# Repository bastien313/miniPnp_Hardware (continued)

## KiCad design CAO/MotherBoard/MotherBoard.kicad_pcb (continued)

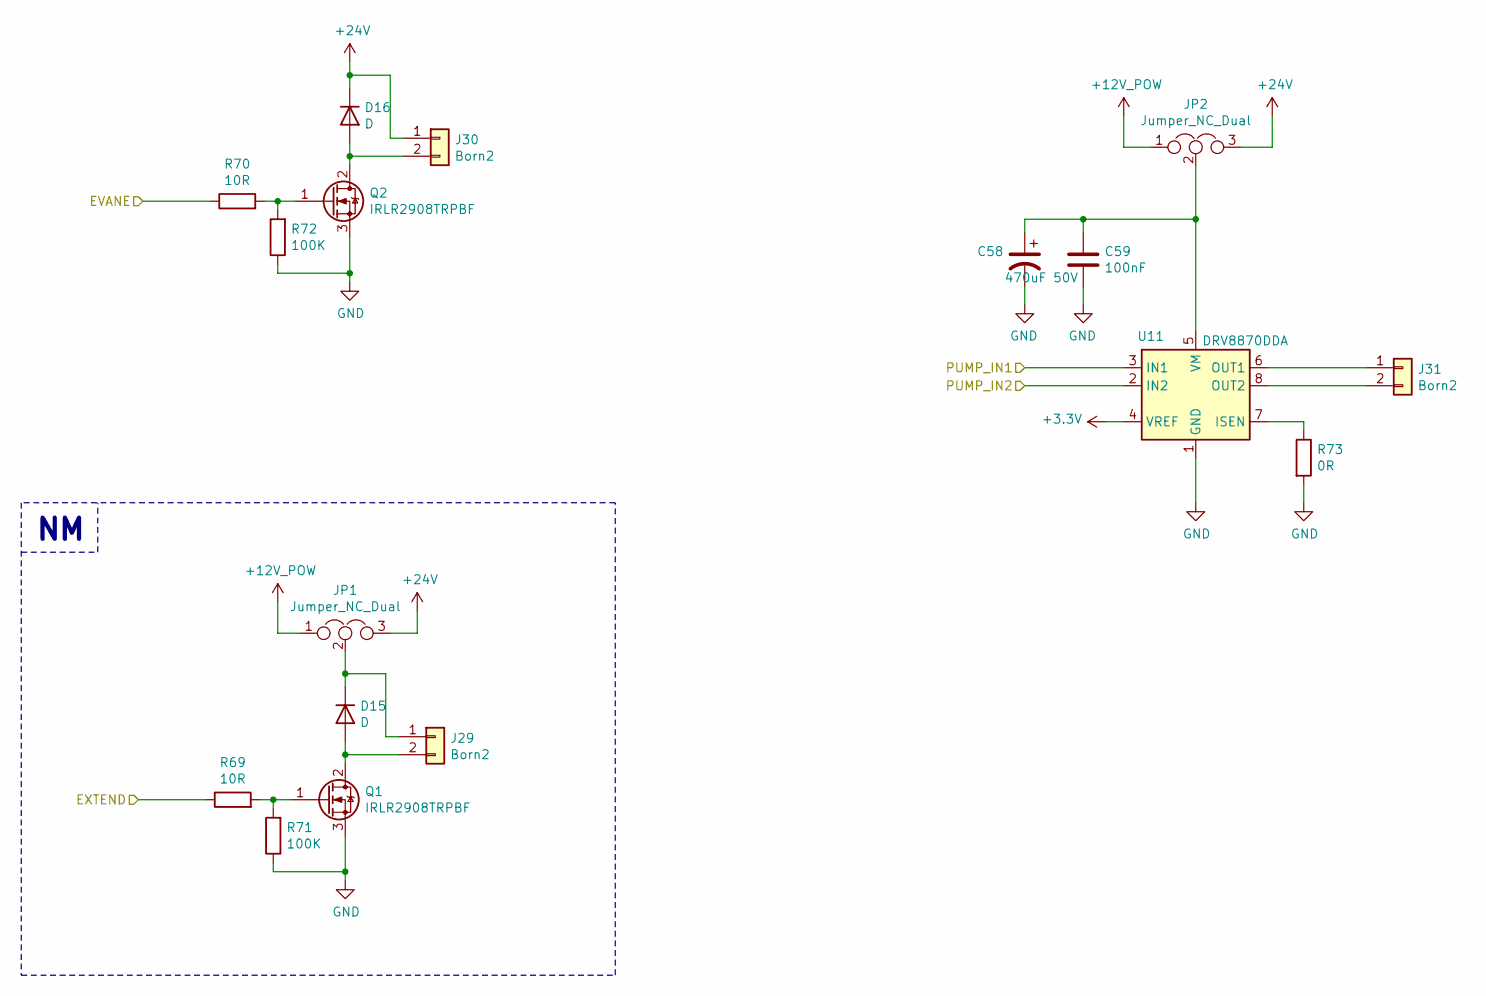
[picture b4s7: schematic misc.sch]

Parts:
C58: 470uF 50V; CP_Radial_D13.0mm_P5.00mm
C59: 100nF; C_0805_2012Metric
D15, D16: D; D_SMB
J29, J30, J31: Born2; TerminalBlock_Phoenix_MKDS-1,5-2-5.08_1x02_P5.08mm_Horizont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
JP1, JP2: Jumper_NC_Dual; PinHeader_1x03_P2.54mm_Vertical
Q1, Q2: IRLR2908TRPBF; TO-252-2
R69, R70: 10R; R_0805_2012Metric_Pad1.15x1.40mm_HandSolder
R71, R72: 100K; R_0805_2012Metric_Pad1.15x1.40mm_HandSolder
R73: 0R; R_2512_6332Metric_Pad1.52x3.35mm_HandSolder
U11: DRV8870DDA; Texas_HTSOP-8-1EP_3.9x4.9mm_P1.27mm_EP2.95x4.9mm_Mask2.4x3.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

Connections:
+12V_POW: JP1.1, JP2.1; also elsewhere on the board
+24V: D16.1 (K), J30.1, JP1.3, JP2.3; also elsewhere on the board
/IO/D20: R70.1; also elsewhere on the board
/IO/D21: R69.1; also elsewhere on the board
/misc/PUMP_IN1: U11.3 (IN1); also elsewhere on the board
/misc/PUMP_IN2: U11.2 (IN2); also elsewhere on the board
unnamed: C58.1, C59.1, JP2.2, U11.5 (VM)
unnamed: D15.1 (K), J29.1, JP1.2
unnamed: D15.2 (A), J29.2, Q1.2 (D)
unnamed: D16.2 (A), J30.2, Q2.2 (D)
unnamed: J31.1, U11.6 (OUT1)
unnamed: J31.2, U11.8 (OUT2)
unnamed: Q1.1 (G), R69.2, R71.2
unnamed: Q2.1 (G), R70.2, R72.2
unnamed: R73.1, U11.7 (ISEN)

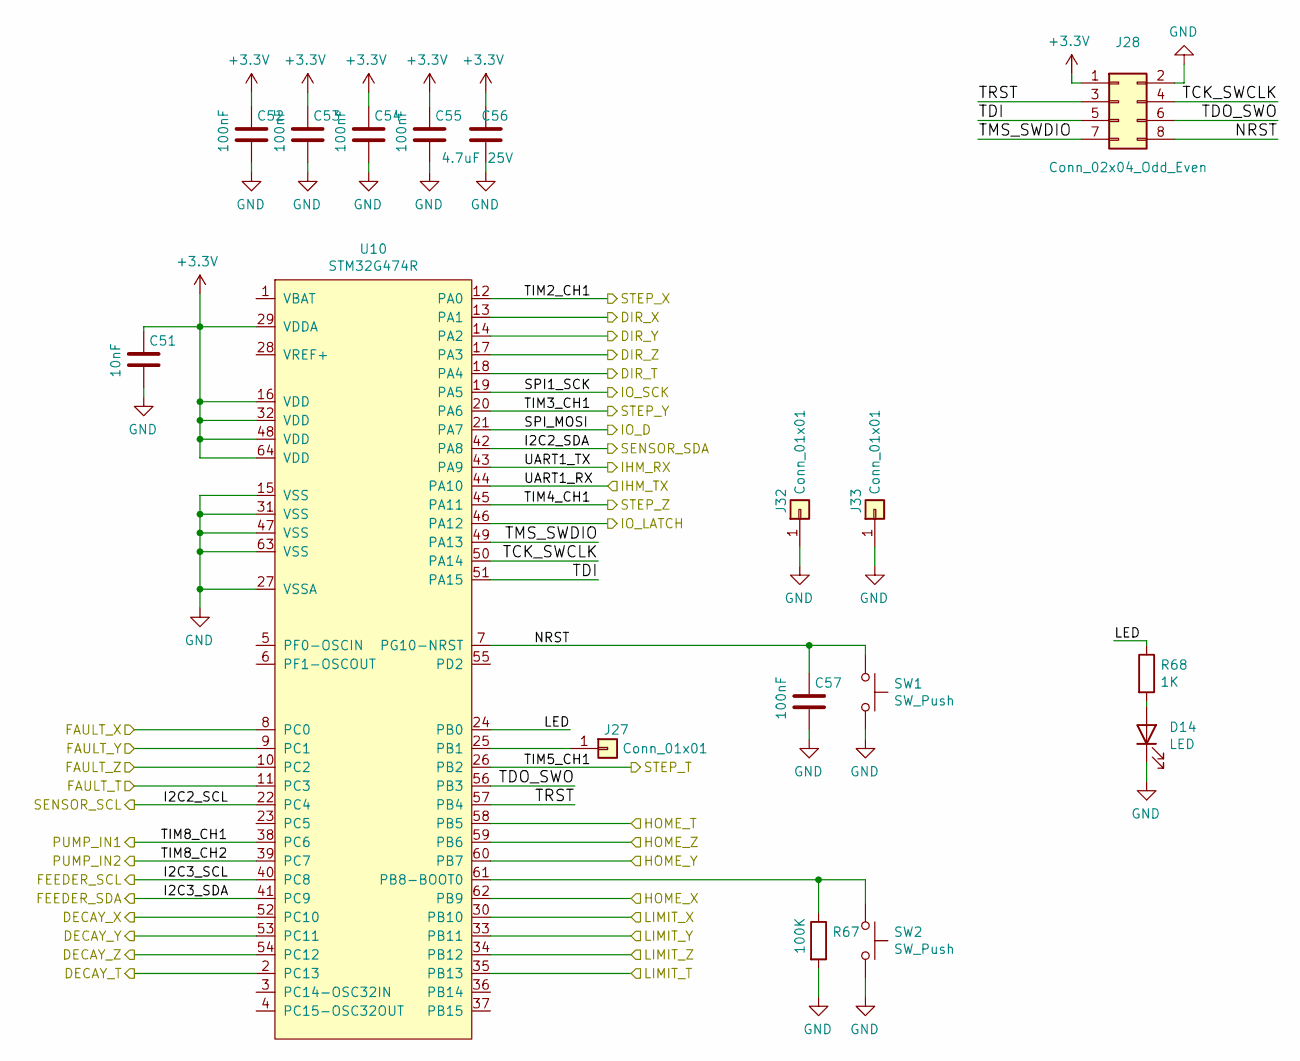
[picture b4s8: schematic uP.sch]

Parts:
C51: 10nF; C_0805_2012Metric
C52, C53, C54, C55, C57: 100nF; C_0805_2012Metric
C56: 4.7uF 25V; C_0805_2012Metric
D14: LED; LED_1206_3216Metric_Castellated
J27, J32, J33: Conn_01x01; Pin_D1.1mm_L8.5mm_W2.5mm_FlatFork
J28: Conn_02x04_Odd_Even; 8Micro-MaTch
R67: 100K; R_0805_2012Metric_Pad1.15x1.40mm_HandSolder
R68: 1K; R_0805_2012Metric_Pad1.15x1.40mm_HandSolder
SW1, SW2: SW_Push; FSM2JSMA
U10: STM32G474R; LQFP-64_10x10mm_P0.5mm

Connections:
/I2C_SENSOR/SCL: U10.22 (PC4); also elsewhere on the board
/I2C_SENSOR/SDA: U10.42 (PA8); also elsewhere on the board
/INPUT/HOME_T: U10.58 (PB5); also elsewhere on the board
/INPUT/HOME_X: U10.62 (PB9); also elsewhere on the board
/IO/CLK: U10.19 (PA5); also elsewhere on the board
/IO/DATA_IN: U10.21 (PA7); also elsewhere on the board
/T/DECAY: U10.2 (PC13); also elsewhere on the board
/T/DIR: U10.18 (PA4); also elsewhere on the board
/T/STEP: U10.26 (PB2); also elsewhere on the board
/X/DECAY: U10.52 (PC10); also elsewhere on the board
/X/DIR: U10.13 (PA1); also elsewhere on the board
/X/STEP: U10.12 (PA0); also elsewhere on the board
/Y/DECAY: U10.53 (PC11); also elsewhere on the board
/Y/DIR: U10.14 (PA2); also elsewhere on the board
/Y/STEP: U10.20 (PA6); also elsewhere on the board
/Z/DECAY: U10.54 (PC12); also elsewhere on the board
/Z/DIR: U10.17 (PA3); also elsewhere on the board
/Z/STEP: U10.45 (PA11); also elsewhere on the board
/misc/PUMP_IN1: U10.38 (PC6); also elsewhere on the board
/misc/PUMP_IN2: U10.39 (PC7); also elsewhere on the board
/uP/FAULT_T: U10.11 (PC3); also elsewhere on the board
/uP/FAULT_X: U10.8 (PC0); also elsewhere on the board
/uP/FAULT_Y: U10.9 (PC1); also elsewhere on the board
/uP/FAULT_Z: U10.10 (PC2); also elsewhere on the board
/uP/FEEDER_SCL: U10.40 (PC8); also elsewhere on the board
/uP/FEEDER_SDA: U10.41 (PC9); also elsewhere on the board
/uP/IHM_RX: U10.43 (PA9); also elsewhere on the board
/uP/IHM_TX: U10.44 (PA10); also elsewhere on the board
/uP/IO_LATCH: U10.46 (PA12); also elsewhere on the board
/uP/LED: R68.1, U10.24 (PB0)
/uP/LIMIT_T: U10.35 (PB13); also elsewhere on the board
/uP/LIMIT_X: U10.30 (PB10); also elsewhere on the board
/uP/LIMIT_Y: U10.33 (PB11); also elsewhere on the board
/uP/LIMIT_Z: U10.34 (PB12); also elsewhere on the board
/uP/NRST: C57.1, J28.8, SW1.1, U10.7 (PG10-NRST)
/uP/TCK_SWCLK: J28.4, U10.50 (PA14)
/uP/TDI: J28.5, U10.51 (PA15)
/uP/TDO_SWO: J28.6, U10.56 (PB3)
/uP/TMS_SWDIO: J28.7, U10.49 (PA13)
/uP/TRST: J28.3, U10.57 (PB4)
unnamed: D14.2 (A), R68.2
unnamed: J27.1, U10.25 (PB1)
unnamed: R67.1, SW2.1, U10.61 (PB8-BOOT0)

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
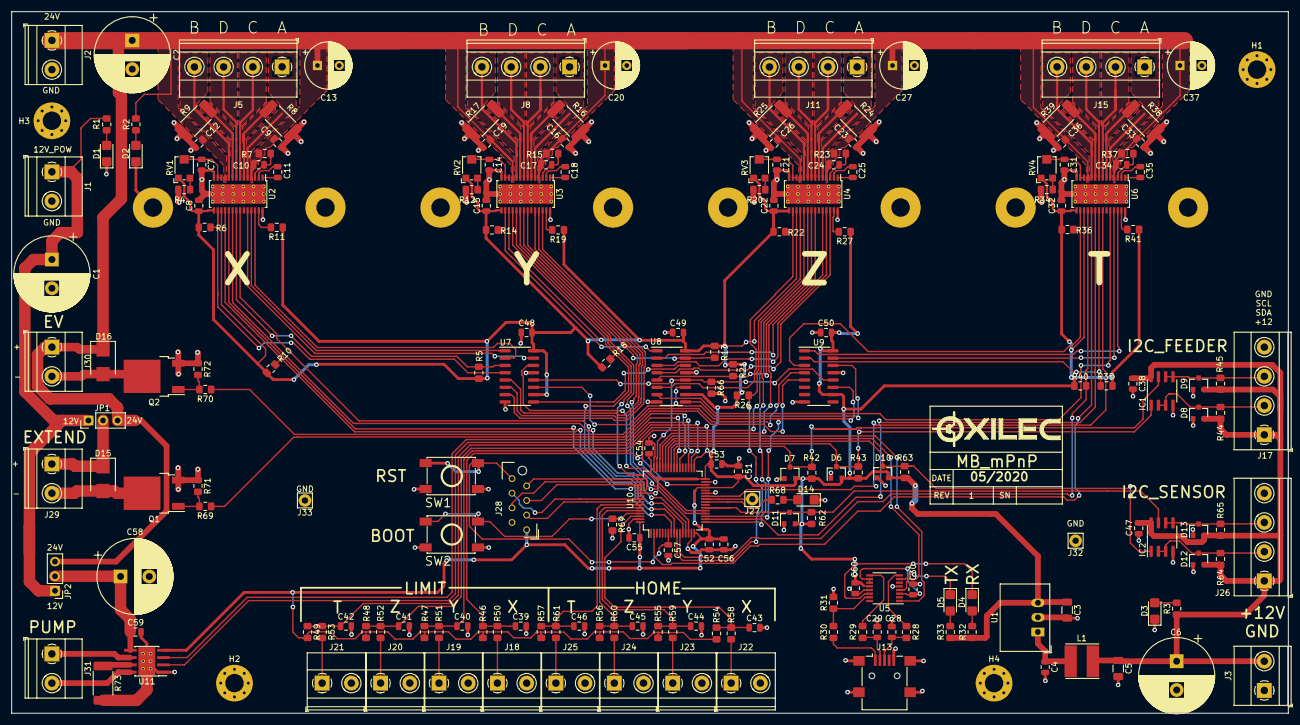
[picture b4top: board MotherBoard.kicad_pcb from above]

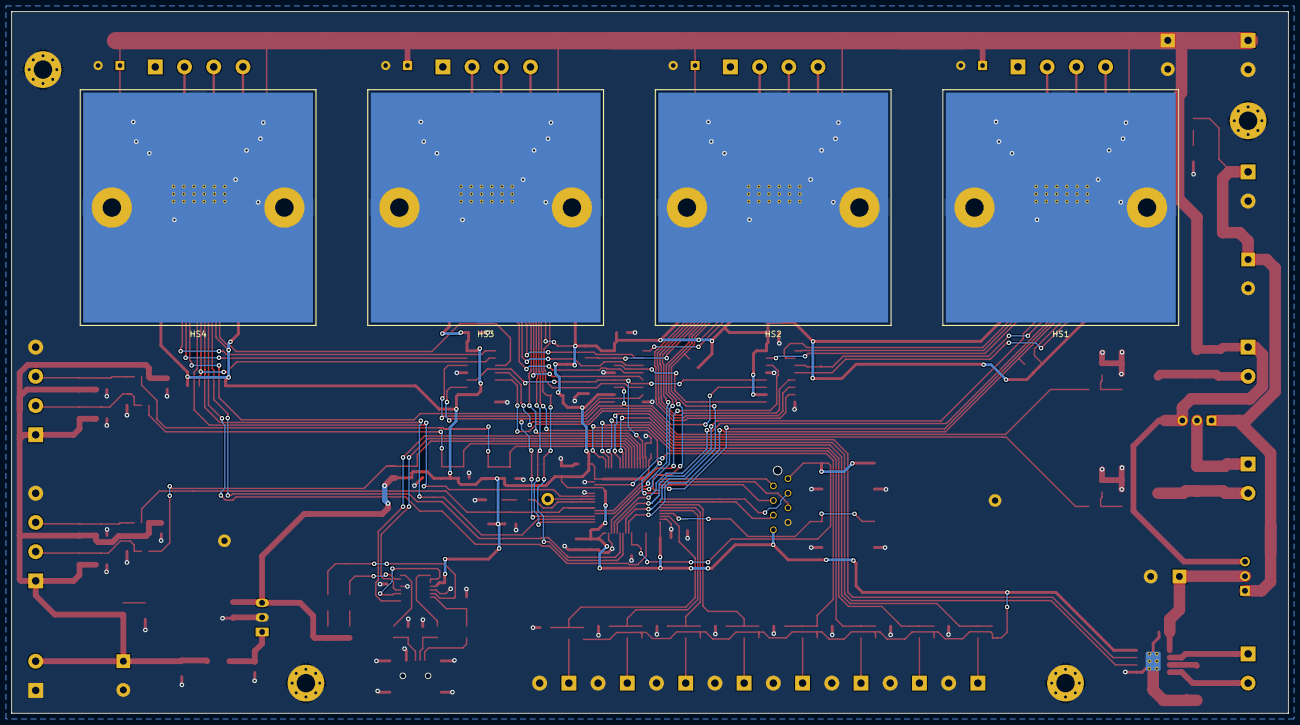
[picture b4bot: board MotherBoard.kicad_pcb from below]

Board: 2 copper layers, 222.0 x 122.0 mm, 214 parts (4 on the bottom side), 158 nets.

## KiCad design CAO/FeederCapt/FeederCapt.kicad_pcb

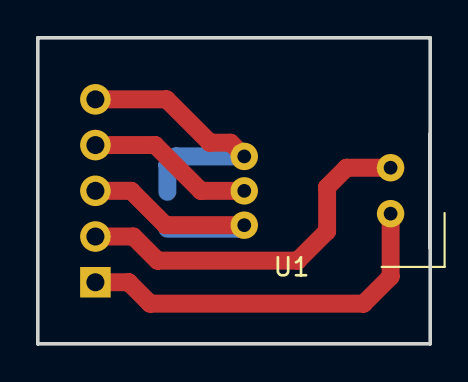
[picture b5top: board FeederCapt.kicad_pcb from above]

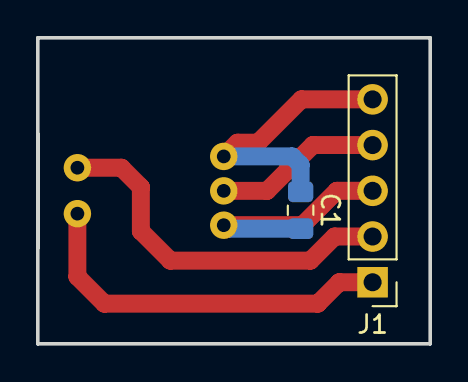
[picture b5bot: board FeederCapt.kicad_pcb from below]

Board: 2 copper layers, 21.8 x 17.0 mm, 3 parts (2 on the bottom side), 5 nets.

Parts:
C1: 100nF; C_0805_2012Metric_Pad1.15x1.40mm_HandSolder
J1: Conn_01x05; PinHeader_1x05_P2.54mm_Vertical
U1: OPB460N11

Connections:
unnamed: C1.1, J1.5, U1.3
unnamed: C1.2, J1.3, U1.5
unnamed: J1.1, U1.1
unnamed: J1.2, U1.2
unnamed: J1.4, U1.4

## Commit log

2022-04-16 hardware V1
2022-04-16 Add VNC doc
